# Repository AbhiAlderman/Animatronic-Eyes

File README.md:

# Animatronic-Eyes
Pair of 3D-printed animatronic eyes equipped with an ESP32-CAM microcontroller. Capable of livestreaming video feed to web server and detecting faces. Uses the position of the face to make the 3D printed eyes "follow" the face.

The main code can be found under Animatronic-Eyes/eyeanimatronic-main/software/accessPointWebServer/accessPointWebServer.ino.

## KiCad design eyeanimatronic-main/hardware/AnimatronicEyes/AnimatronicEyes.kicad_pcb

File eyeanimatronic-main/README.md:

# eyeanimatronic
HOPE Sp22 Animatronic Files

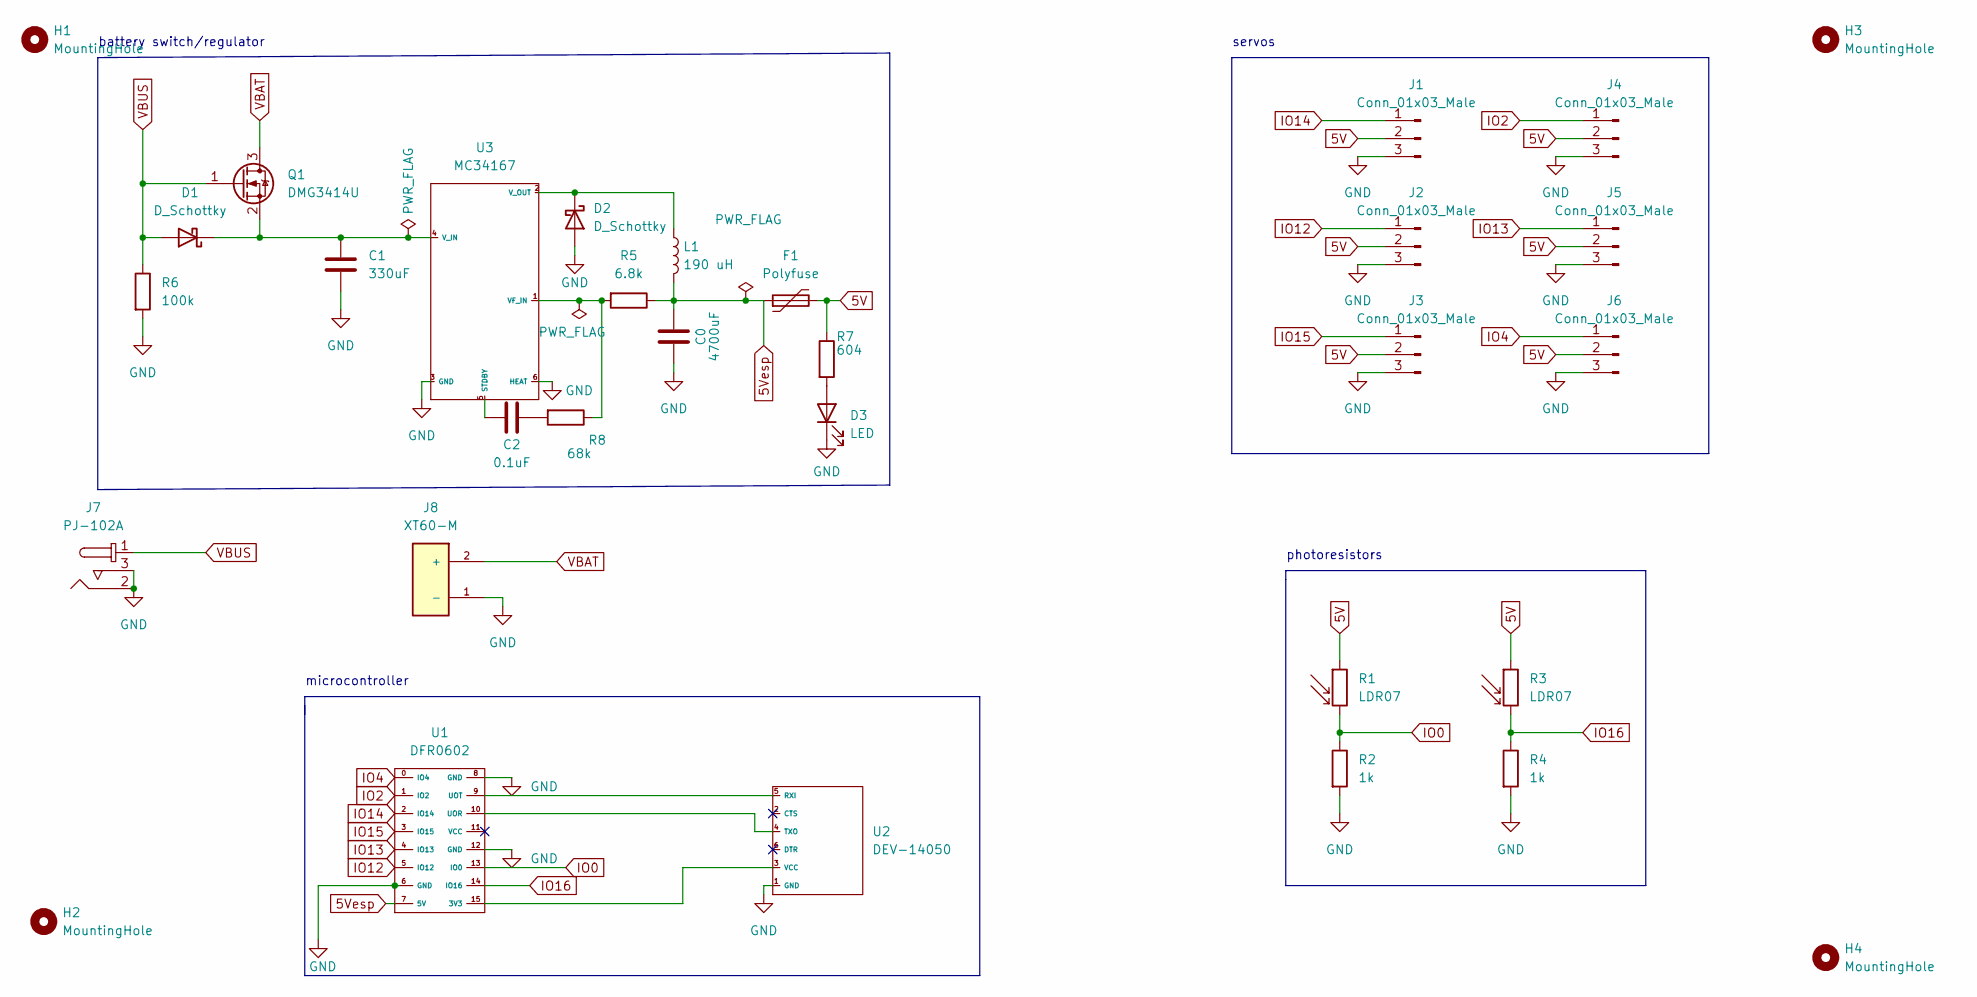
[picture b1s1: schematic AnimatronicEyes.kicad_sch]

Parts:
C0: 4700uF; CP_Radial_D16.0mm_P7.50mm
C1: 330uF; CP_Radial_D10.0mm_P5.00mm
C2: 0.1uF; C_0603_1608Metric
D1, D2: D_Schottky; D_SMA
D3: LED; LED_0603_1608Metric
F1: Polyfuse; Fuse_0805_2012Metric
H1, H2, H3, H4: MountingHole; MountingHole_2.1mm
J1, J2, J3, J4, J5, J6: Conn_01x03_Male; FanPinHeader_1x03_P2.54mm_Vertical
J7: PJ-102A; barreljack-eye; MPN PJ-102A; Digi-Key_PN CP-102A-ND
J8: XT60-M; PARTREV 1.2
L1: 190 uH; SRR1280-181K
Q1: DMG3414U; SOT-23
R1, R3: LDR07; R_LDR_5.1x4.3mm_P3.4mm_Vertical
R2, R4: 1k; R_0603_1608Metric
R5: 6.8k; R_0603_1608Metric
R6: 100k; R_0603_1608Metric
R7: 604; R_0603_1608Metric
R8: 68k; R_0603_1608Metric
U1: DFR0602; ESP32-Cam
U2: DEV-14050; PinHeader_1x06_P2.54mm_Vertical
U3: MC34167; MC34167 - 5V StepDownRegulator

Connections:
5V: F1.2, J1.2, J2.2, J3.2, J4.2, J5.2, J6.2, R1.1, R3.1, R7.1
5Vesp: C0.2, F1.1, L1.2, R5.1, U1.7 (5V)
GND: C0.1, C1.2, D2.2 (A), D3.1 (K), J1.3, J2.3, J3.3, J4.3, J5.3, J6.3, J7.2, J7.3, J8.1 (-), R2.2, R4.2, R6.2, U1.6 (GND), U1.8 (GND), U1.12 (GND), U2.1 (GND), U3.3 (GND), U3.6 (HEAT)
IO0: R1.2, R2.1, U1.13 (IO0)
IO2: J4.1, U1.1 (IO2)
IO4: J6.1, U1.0 (IO4)
IO12: J2.1, U1.5 (IO12)
IO13: J5.1, U1.4 (IO13)
IO14: J1.1, U1.2 (IO14)
IO15: J3.1, U1.3 (IO15)
IO16: R3.2, R4.1, U1.14 (IO16)
unnamed: C1.1, D1.1 (K), Q1.2 (S), U3.4 (V_IN)
unnamed: C2.1, U3.5 (STDBY)
unnamed: C2.2, R8.2
unnamed: D2.1 (K), L1.1, U3.2 (V_OUT)
unnamed: D3.2 (A), R7.2
unnamed: R5.2, R8.1, U3.1 (VF_IN)
unnamed: U1.9 (UOT), U2.5 (RXI)
unnamed: U1.10 (UOR), U2.4 (TXO)
unnamed: U1.15 (3V3), U2.3 (VCC)
VBAT: J8.2 (+), Q1.3 (D)
VBUS: D1.2 (A), J7.1, Q1.1 (G), R6.1

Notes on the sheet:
servos
microcontroller
battery switch/regulator
photoresistors

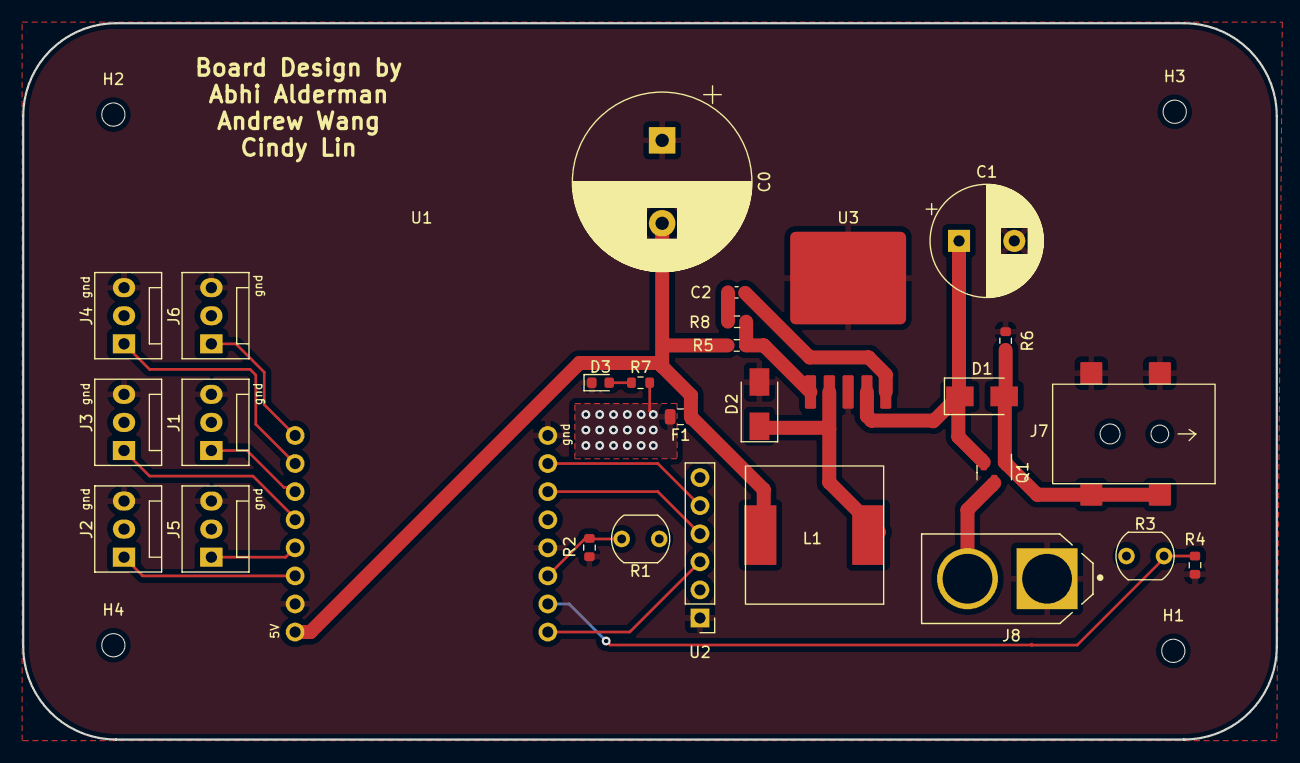
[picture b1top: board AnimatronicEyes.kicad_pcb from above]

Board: 2 copper layers, 113.4 x 64.8 mm, 32 parts (0 on the bottom side), 22 nets.

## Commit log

2022-05-24 Add files via upload
    Imported files from Andrew's repository into my own.
